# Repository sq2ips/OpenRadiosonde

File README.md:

# OpenRadiosonde

This project has a goal of making a open source amateur radiosonde project for high altitude balloon flights with telemetry and images downlink.

# Main features:
  - Dual band 100mW transmitter 2m and 70cm
  - Horus Binary V3 4FSK and AFSK APRS telemetry encoder
  - SSTV encoder
  - camera and other sensors connector
  - Battery voltage ADC
  - GPS positioning

# Hardware
  - STM32L476RGT6 MCU
  - SI4468-A2A-IMR Radio transmitter
  - 30MHz TCXO
  - u-blox GPS???
  - camera?
  - PSU?

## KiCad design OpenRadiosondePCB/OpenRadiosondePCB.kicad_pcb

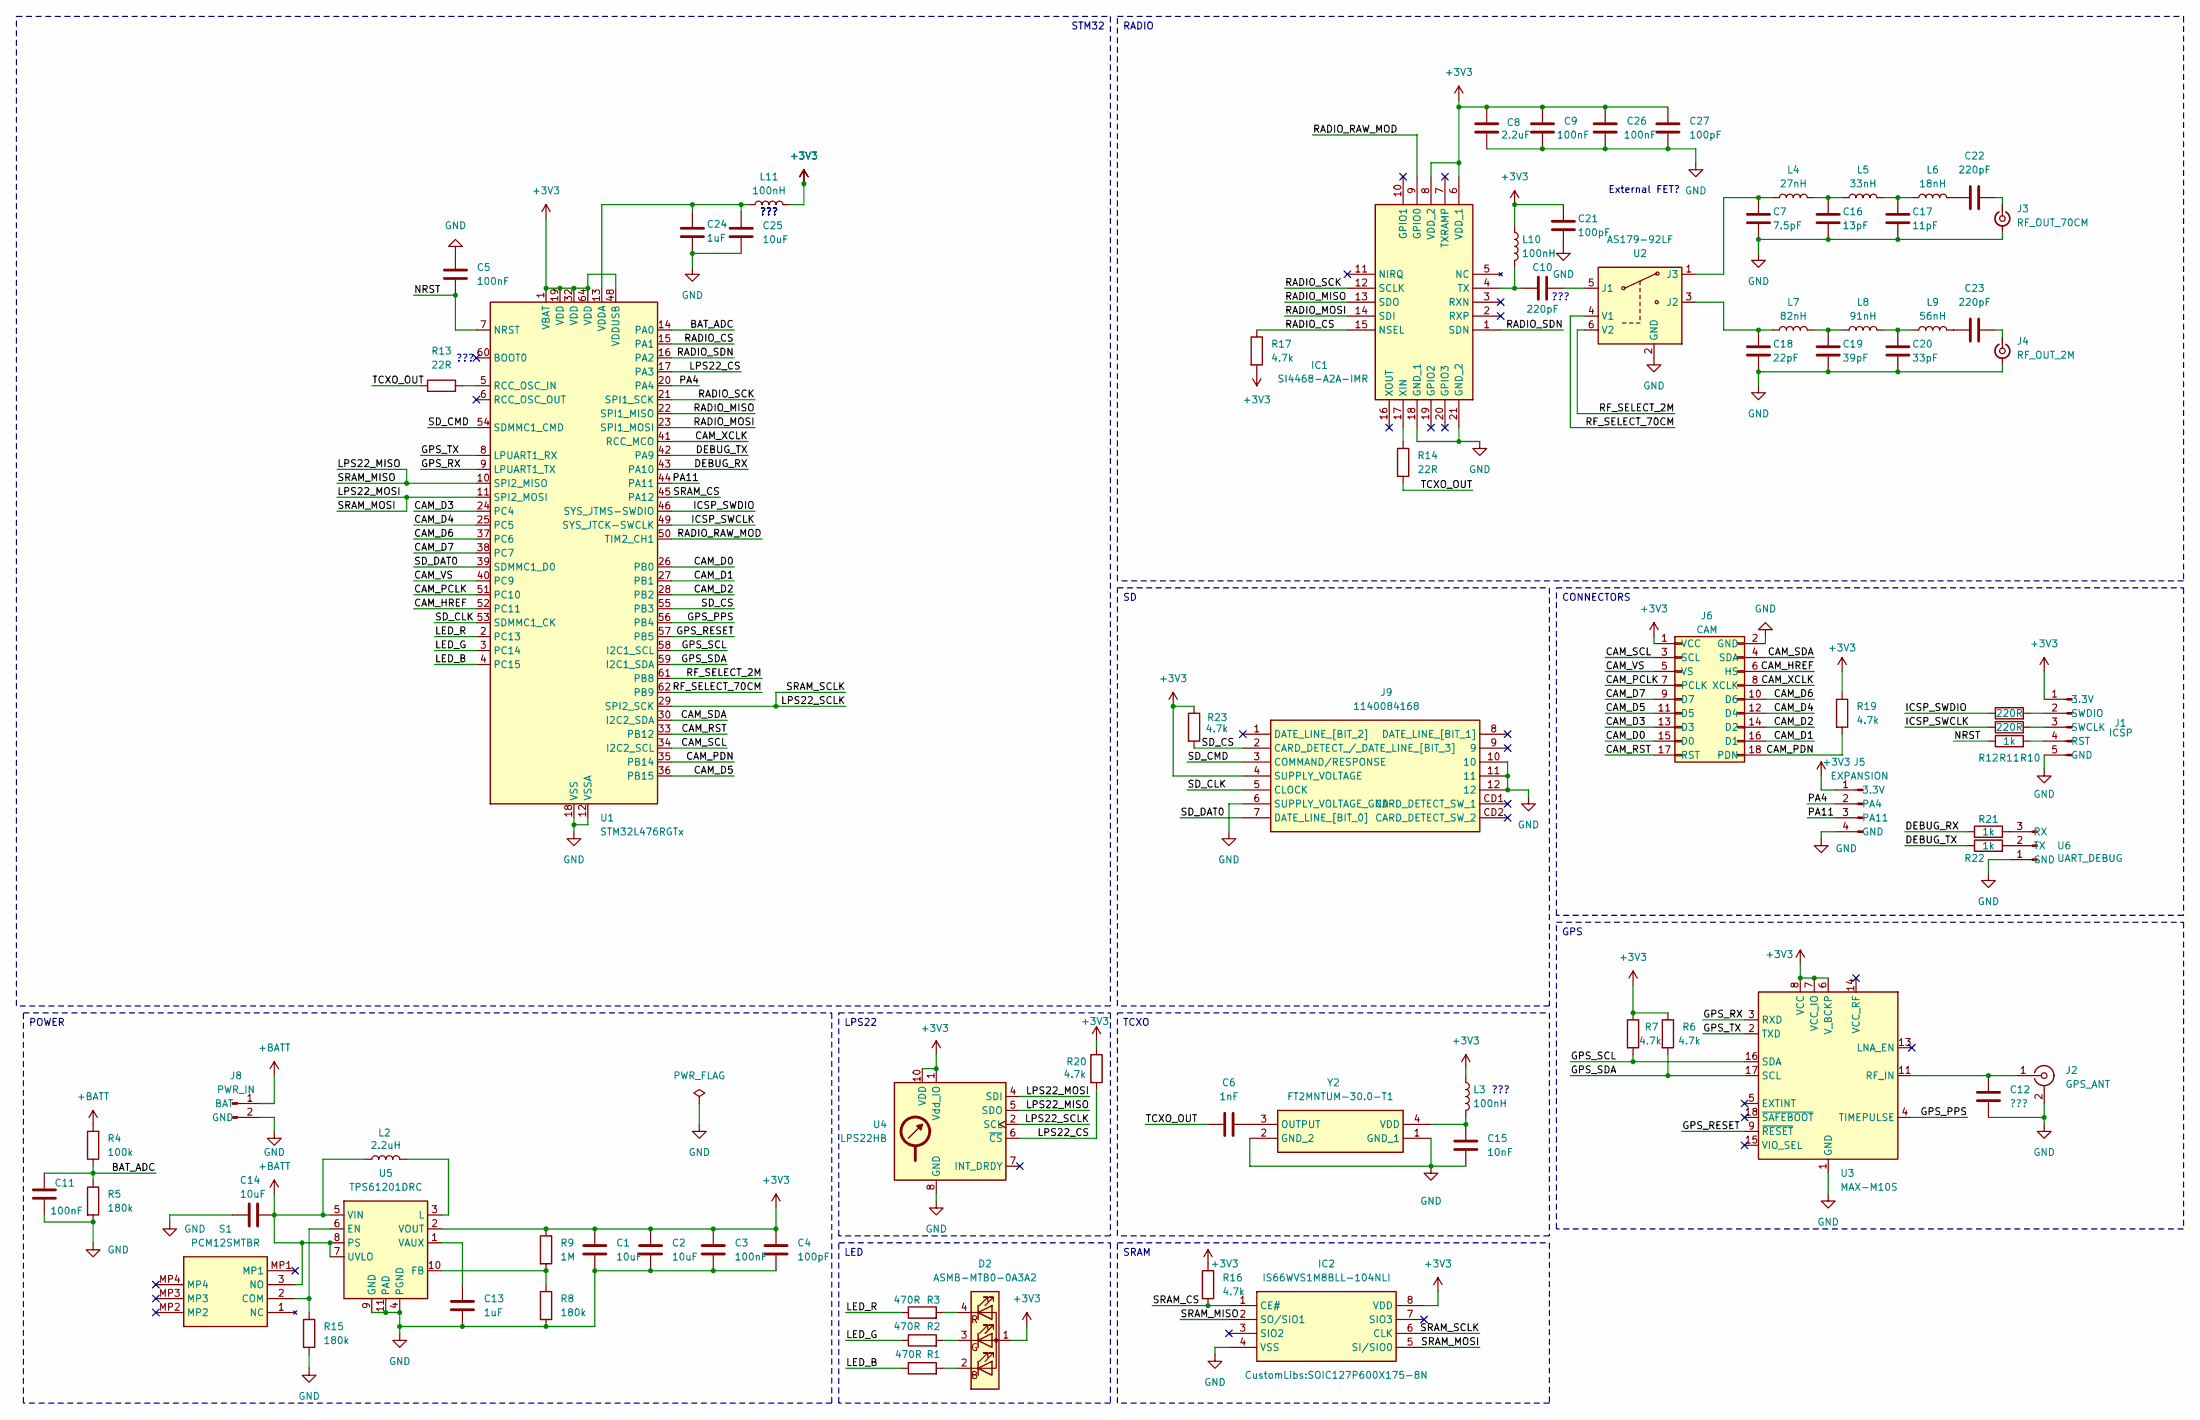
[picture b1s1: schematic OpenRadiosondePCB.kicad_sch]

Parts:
C1, C2, C14, C25: 10uF; C_0603_1608Metric
C3, C5, C9, C11, C26: 100nF; C_0603_1608Metric
C4, C21, C27: 100pF; C_0603_1608Metric
C6: 1nF; C_0603_1608Metric
C7: 7.5pF; C_0603_1608Metric
C8: 2.2uF; C_0603_1608Metric
C10, C22, C23: 220pF; C_0603_1608Metric
C12: ???; C_0603_1608Metric
C13, C24: 1uF; C_0603_1608Metric
C15: 10nF; C_0603_1608Metric
C16: 13pF; C_0603_1608Metric
C17: 11pF; C_0603_1608Metric
C18: 22pF; C_0603_1608Metric
C19: 39pF; C_0603_1608Metric
C20: 33pF; C_0603_1608Metric
D2: ASMB-MTB0-0A3A2; LED_Avago_PLCC4_3.2x2.8mm_CW
IC1: SI4468-A2A-IMR; QFN50P400X400X90-21N; Mouser Part Number 634-SI4468-A2A-IMR
IC2: IS66WVS1M8BLL-104NLI; SOIC127P600X175-8N; Mouser Part Number 870-ISS1M8BLL-104NLI
J1: ICSP; PinHeader_1x05_P2.54mm_Vertical
J2: GPS_ANT; U.FL_Hirose_U.FL-R-SMT-1_Vertical
J3: RF_OUT_70CM; SMA_Molex_73251-1153_EdgeMount_Horizontal
J4: RF_OUT_2M; SMA_Molex_73251-1153_EdgeMount_Horizontal
J5: EXPANSION; PinHeader_1x04_P2.54mm_Vertical
J6: CAM; PinHeader_2x09_P2.54mm_Vertical
J8: PWR_IN; PinHeader_1x02_P2.54mm_Vertical
J9: 1140084168; Mouser Part Number 523-114-00841-68
L2: 2.2uH; LPS3015
L3, L10, L11: 100nH; L_0603_1608Metric
L4: 27nH; L_0603_1608Metric
L5: 33nH; L_0603_1608Metric
L6: 18nH; L_0603_1608Metric
L7: 82nH; L_0603_1608Metric
L8: 91nH; L_0603_1608Metric
L9: 56nH; L_0603_1608Metric
R1, R2, R3: 470R; R_0603_1608Metric
R4: 100k; R_0603_1608Metric
R5, R8, R15: 180k; R_0603_1608Metric
R6, R7, R16, R17, R19, R20, R23: 4.7k; R_0603_1608Metric
R9: 1M; R_0603_1608Metric
R10, R21, R22: 1k; R_0603_1608Metric
R11, R12: 220R; R_0603_1608Metric
R13, R14: 22R; R_0603_1608Metric
S1: PCM12SMTBR; Mouser Part Number 611-PCM12SMTBR
U1: STM32L476RGTx; LQFP-64_10x10mm_P0.5mm
U2: AS179-92LF; SOT-363_SC-70-6
U3: MAX-M10S; ublox_MAX
U4: LPS22HB; ST_HLGA-10_2x2mm_P0.5mm_LayoutBorder3x2y
U5: TPS61201DRC; Texas_S-PVSON-N10_ThermalVias
U6: UART_DEBUG; PinHeader_1x03_P2.54mm_Vertical
Y2: FT2MNTUM-30.0-T1; FT2MNTUM300T1; Mouser Part Number 815-FT2MNTUM-30.0-T1

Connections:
+3V3: C1.1, C2.1, C3.1, C4.1, C8.1, C9.1, C21.1, C26.1, C27.1, D2.1 (A), IC1.6 (VDD_1), IC1.8 (VDD_2), IC2.8 (VDD), J1.1 (3.3V), J5.1 (3.3V), J6.1 (VCC), J9.4 (SUPPLY_VOLTAGE), L3.1, L10.1, L11.2, R6.1, R7.1, R9.1, R16.1, R17.2, R19.1, R20.1, R23.1, U1.1 (VBAT), U1.19 (VDD), U1.32 (VDD), U1.48 (VDDUSB), U1.64 (VDD), U3.6 (V_BCKP), U3.7 (VCC_IO), U3.8 (VCC), U4.1 (Vdd_IO), U4.10 (VDD), U5.2 (VOUT)
+BATT: C14.1, J8.1 (BAT), L2.1, R4.2, S1.3 (NO), U5.5 (VIN), U5.7 (UVLO), U5.8 (PS)
/BAT_ADC: C11.1, R4.1, R5.1, U1.14 (PA0)
/CAM_D0: J6.15 (D0), U1.26 (PB0)
/CAM_D1: J6.16 (D1), U1.27 (PB1)
/CAM_D2: J6.14 (D2), U1.28 (PB2)
/CAM_D3: J6.13 (D3), U1.24 (PC4)
/CAM_D4: J6.12 (D4), U1.25 (PC5)
/CAM_D5: J6.11 (D5), U1.36 (PB15)
/CAM_D6: J6.10 (D6), U1.37 (PC6)
/CAM_D7: J6.9 (D7), U1.38 (PC7)
/CAM_HREF: J6.6 (HS), U1.52 (PC11)
/CAM_PCLK: J6.7 (PCLK), U1.51 (PC10)
/CAM_PDN: J6.18 (PDN), R19.2, U1.35 (PB14)
/CAM_RST: J6.17 (RST), U1.33 (PB12)
/CAM_SCL: J6.3 (SCL), U1.34 (I2C2_SCL)
/CAM_SDA: J6.4 (SDA), U1.30 (I2C2_SDA)
/CAM_VS: J6.5 (VS), U1.40 (PC9)
/CAM_XCLK: J6.8 (XCLK), U1.41 (RCC_MCO)
/DEBUG_RX: R21.1, U1.43 (PA10)
/DEBUG_TX: R22.1, U1.42 (PA9)
/GPS_PPS: U1.56 (PB4), U3.4 (TIMEPULSE)
/GPS_RESET: U1.57 (PB5), U3.9 (~RESET)
/GPS_RX: U1.9 (LPUART1_TX), U3.3 (RXD)
/GPS_SCL: R7.2, U1.58 (I2C1_SCL), U3.16 (SDA)
/GPS_SDA: R6.2, U1.59 (I2C1_SDA), U3.17 (SCL)
/GPS_TX: U1.8 (LPUART1_RX), U3.2 (TXD)
/ICSP_SWCLK: R11.1, U1.49 (SYS_JTCK-SWCLK)
/ICSP_SWDIO: R12.1, U1.46 (SYS_JTMS-SWDIO)
/LED_B: R1.1, U1.4 (PC15)
/LED_G: R2.1, U1.3 (PC14)
/LED_R: R3.1, U1.2 (PC13)
/LPS22_CS: R20.2, U1.17 (PA3), U4.6 (~CS)
/LPS22_MISO: IC2.2 (SO/SIO1), U1.10 (SPI2_MISO), U4.5 (SDO)
/LPS22_MOSI: IC2.5 (SI/SIO0), U1.11 (SPI2_MOSI), U4.4 (SDI)
/LPS22_SCLK: IC2.6 (CLK), U1.29 (SPI2_SCK), U4.2 (SCL)
/NRST: C5.2, R10.1, U1.7 (NRST)
/PA4: J5.2 (PA4), U1.20 (PA4)
/PA11: J5.3 (PA11), U1.44 (PA11)
/RADIO_CS: IC1.15 (NSEL), R17.1, U1.15 (PA1)
/RADIO_MISO: IC1.13 (SDO), U1.22 (SPI1_MISO)
/RADIO_MOSI: IC1.14 (SDI), U1.23 (SPI1_MOSI)
/RADIO_RAW_MOD: IC1.9 (GPIO0), U1.50 (TIM2_CH1)
/RADIO_SCK: IC1.12 (SCLK), U1.21 (SPI1_SCK)
/RADIO_SDN: IC1.1 (SDN), U1.16 (PA2)
/RF_SELECT_2M: U1.61 (PB8), U2.6 (V2)
/RF_SELECT_70CM: U1.62 (PB9), U2.4 (V1)
/SD_CLK: J9.5 (CLOCK), U1.53 (SDMMC1_CK)
/SD_CMD: J9.3 (COMMAND/RESPONSE), U1.54 (SDMMC1_CMD)
/SD_CS: J9.2 (CARD_DETECT_/_DATE_LINE_[BIT_3]), R23.2, U1.55 (PB3)
/SD_DAT0: J9.7 (DATE_LINE_[BIT_0]), U1.39 (SDMMC1_D0)
/SRAM_CS: IC2.1 (CE#), R16.2, U1.45 (PA12)
/TCXO_OUT: C6.2, R13.1, R14.2
GND: C1.2, C2.2, C3.2, C4.2, C5.1, C7.2, C8.2, C9.2, C11.2, C12.2, C13.1, C14.2, C15.2, C16.2, C17.2, C18.2, C19.2, C20.2, C21.2, C24.2, C25.2, C26.2, C27.2, IC1.18 (GND_1), IC1.21 (GND_2), IC2.4 (VSS), J1.5 (GND), J2.2 (Ext), J3.2 (Ext), J4.2 (Ext), J5.4 (GND), J6.2 (GND), J8.2 (GND), J9.6 (SUPPLY_VOLTAGE_GND), J9.10, J9.11, J9.12, R5.2, R8.2, R15.2, U1.12 (VSSA), U1.18 (VSS), U1.31 (VSS), U1.47 (VSS), U1.63 (VSS), U2.2 (GND), U3.1 (GND), U3.10 (GND), U3.12 (GND), U4.3 (GND), U4.8 (GND), U4.9 (GND), U5.4 (PGND), U5.9 (GND), U5.11 (PAD), U6.1 (GND), Y2.1 (GND_1), Y2.2 (GND_2)
unnamed: C16.1, L4.2, L5.1
unnamed: C17.1, L5.2, L6.1
unnamed: C19.1, L7.2, L8.1
unnamed: C20.1, L8.2, L9.1
unnamed: C22.1, L6.2
unnamed: C23.1, L9.2
unnamed: D2.2 (BK), R1.2
unnamed: D2.3 (GK), R2.2
unnamed: D2.4 (RK), R3.2
unnamed: C10.1, IC1.4 (TX), L10.2
unnamed: IC1.17 (XIN), R14.1
unnamed: J1.4 (RST), R10.2
unnamed: J1.3 (SWCLK), R11.2
unnamed: J1.2 (SWDIO), R12.2
unnamed: C12.1, J2.1 (In), U3.11 (RF_IN)
unnamed: C22.2, J3.1 (In)
unnamed: C23.2, J4.1 (In)
unnamed: R15.1, S1.2 (COM), U5.6 (EN)
unnamed: R13.2, U1.5 (RCC_OSC_IN)
unnamed: C24.1, C25.1, L11.1, U1.13 (VDDA)
unnamed: C10.2, U2.5 (J1)
unnamed: C18.1, L7.1, U2.3 (J2)
unnamed: C7.1, L4.1, U2.1 (J3)
unnamed: R8.1, R9.2, U5.10 (FB)
unnamed: L2.2, U5.3 (L)
unnamed: C13.2, U5.1 (VAUX)
unnamed: R21.2, U6.3 (RX)
unnamed: R22.2, U6.2 (TX)
unnamed: C6.1, Y2.3 (OUTPUT)
unnamed: C15.1, L3.2, Y2.4 (VDD)

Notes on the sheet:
???
???
External FET?
TCXO
POWER
SRAM
STM32
LED
CONNECTORS
LPS22
GPS
RADIO

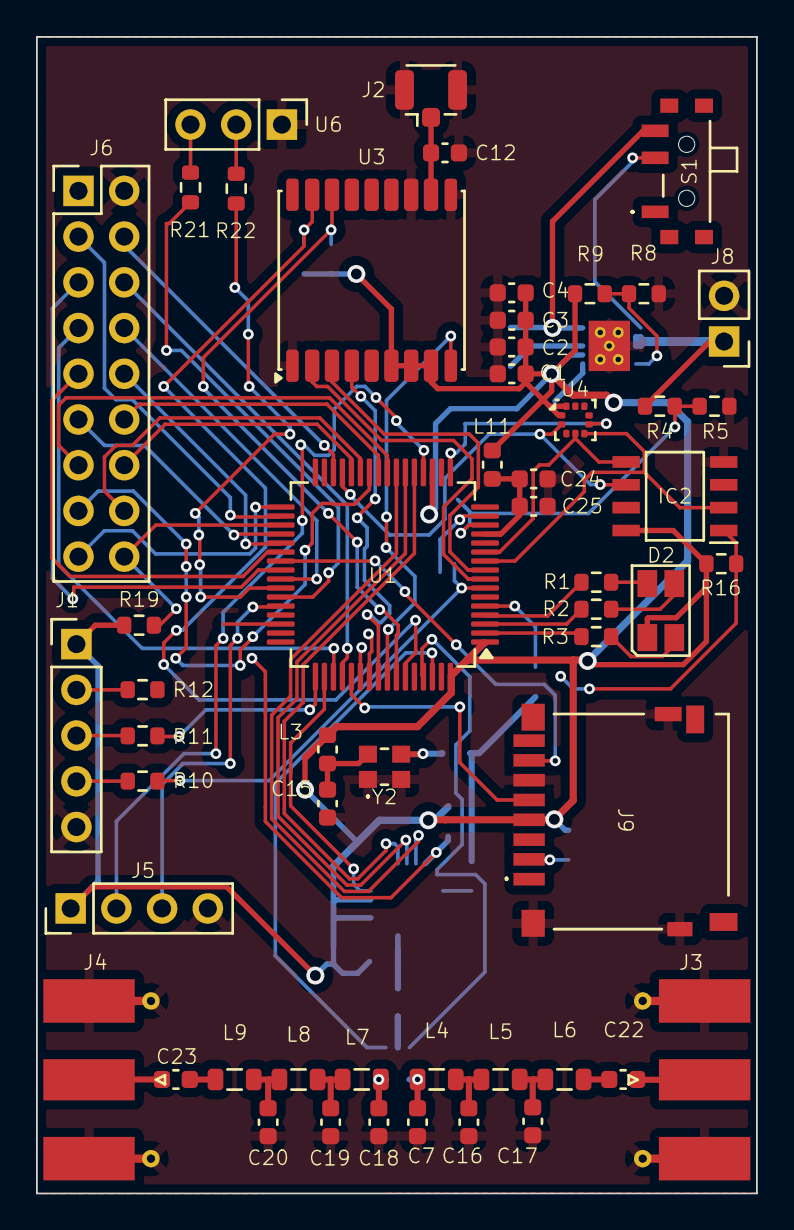
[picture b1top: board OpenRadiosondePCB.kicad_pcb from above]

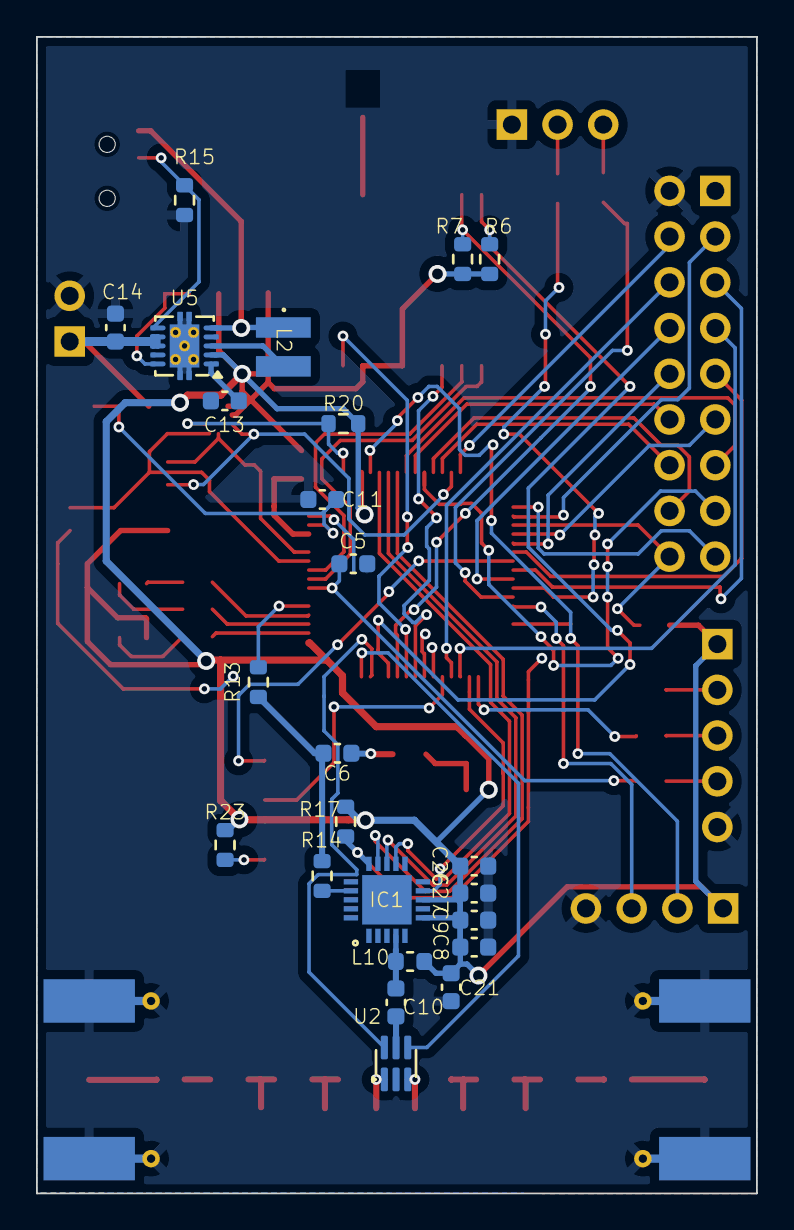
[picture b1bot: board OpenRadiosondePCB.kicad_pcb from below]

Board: 2 copper layers, 40.0 x 64.2 mm, 78 parts (24 on the bottom side), 84 nets.

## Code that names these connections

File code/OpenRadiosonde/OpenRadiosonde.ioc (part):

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Mcu.Name=STM32L476R(C-E-G)Tx
Mcu.Package=LQFP64
Mcu.UserName=STM32L476RGTx
PA0.GPIOParameters=GPIO_Label
PA0.GPIO_Label=BAT_ADC
PA0.Signal=ADCx_IN5
PA1.GPIOParameters=GPIO_Label
PA1.GPIO_Label=RADIO_CS
PA1.Signal=GPIO_Output
PA10.Mode=Asynchronous
PA10.Signal=USART1_RX
PA13\ (JTMS-SWDIO).Mode=Serial_Wire
PA13\ (JTMS-SWDIO).Signal=SYS_JTMS-SWDIO
PA14\ (JTCK-SWCLK).Mode=Serial_Wire
PA14\ (JTCK-SWCLK).Signal=SYS_JTCK-SWCLK
PA15\ (JTDI).GPIOParameters=GPIO_Label
PA15\ (JTDI).GPIO_Label=RADIO_RAW_MOD
PA15\ (JTDI).Signal=S_TIM2_CH1
PA2.GPIOParameters=GPIO_Label
PA2.GPIO_Label=RADIO_SDN
PA2.Signal=GPIO_Output
PA3.GPIOParameters=GPIO_Label
PA3.GPIO_Label=LPS22_CS
PA3.Signal=GPIO_Output
PA5.GPIOParameters=GPIO_Label
PA5.GPIO_Label=RADIO_SCK
PA5.Mode=Full_Duplex_Master
PA5.Signal=SPI1_SCK
PA6.GPIOParameters=GPIO_Label
PA6.GPIO_Label=RADIO_MISO
PA6.Mode=Full_Duplex_Master
PA6.Signal=SPI1_MISO
PA7.GPIOParameters=GPIO_Label
PA7.GPIO_Label=RADIO_MOSI
PA7.Mode=Full_Duplex_Master
PA7.Signal=SPI1_MOSI
PA8.GPIOParameters=GPIO_Label
PA8.GPIO_Label=CAM_XCLK
PA8.Mode=Clock-out
PA8.Signal=RCC_MCO
PA9.Mode=Asynchronous
PA9.Signal=USART1_TX
PB0.GPIOParameters=GPIO_Label
PB0.GPIO_Label=CAM_D0
PB0.Signal=GPIO_Input
PB1.GPIOParameters=GPIO_Label
PB1.GPIO_Label=CAM_D1
PB1.Signal=GPIO_Input
PB10.GPIOParameters=GPIO_Label
PB10.GPIO_Label=LPS22_SCK
PB10.Mode=Full_Duplex_Master
PB10.Signal=SPI2_SCK
PB11.GPIOParameters=GPIO_Label
PB11.GPIO_Label=CAM_SDA
PB11.Mode=I2C
PB11.Signal=I2C2_SDA
PB12.GPIOParameters=GPIO_Label
PB12.GPIO_Label=CAM_RST
PB12.Signal=GPIO_Output
PB13.GPIOParameters=GPIO_Label
PB13.GPIO_Label=CAM_SCL
PB13.Mode=I2C
PB13.Signal=I2C2_SCL
PB14.GPIOParameters=GPIO_Label
PB14.GPIO_Label=CAM_PDN
PB14.Signal=GPIO_Output
PB15.GPIOParameters=GPIO_Label
PB15.GPIO_Label=CAM_D5
PB15.Signal=GPIO_Input
PB2.GPIOParameters=GPIO_Label
PB2.GPIO_Label=CAM_D2
PB2.Signal=GPIO_Input
PB3\ (JTDO-TRACESWO).GPIOParameters=GPIO_Label
PB3\ (JTDO-TRACESWO).GPIO_Label=SD_CS
PB3\ (JTDO-TRACESWO).Signal=GPIO_Output
PB4\ (NJTRST).GPIOParameters=GPIO_Label
PB4\ (NJTRST).GPIO_Label=GPS_PPS
PB4\ (NJTRST).Signal=GPXTI4
PB5.GPIOParameters=GPIO_Label
PB5.GPIO_Label=GPS_RESET
PB5.Signal=GPIO_Output
PB6.Mode=I2C
PB6.Signal=I2C1_SCL
PB7.Mode=I2C
PB7.Signal=I2C1_SDA
PB8.GPIOParameters=GPIO_Label
PB8.GPIO_Label=RADIO_SELECT_2M
PB8.Signal=GPIO_Output
PB9.GPIOParameters=GPIO_Label
PB9.GPIO_Label=RADIO_SELECT_70CM
PB9.Signal=GPIO_Output
PC0.GPIOParameters=GPIO_Label
PC0.GPIO_Label=GPS_MRX
PC0.Mode=Asynchronous
PC0.Signal=LPUART1_RX
PC1.GPIOParameters=GPIO_Label
PC1.GPIO_Label=GPS_MTX
PC1.Mode=Asynchronous
PC1.Signal=LPUART1_TX
PC10.GPIOParameters=GPIO_Label
PC10.GPIO_Label=CAM_HREF
PC10.Signal=GPIO_Output
PC11.GPIOParameters=GPIO_Label
PC11.GPIO_Label=CAM_PCLK
PC11.Signal=GPIO_Input
PC12.Mode=SD_1_bit
PC12.Signal=SDMMC1_CK
PC13.GPIOParameters=GPIO_Label
PC13.GPIO_Label=LED_R
PC13.Signal=GPIO_Output
PC14-OSC32_IN\ (PC14).GPIOParameters=GPIO_Label
PC14-OSC32_IN\ (PC14).GPIO_Label=LED_G
PC14-OSC32_IN\ (PC14).Signal=GPIO_Output
PC15-OSC32_OUT\ (PC15).GPIOParameters=GPIO_Label
PC15-OSC32_OUT\ (PC15).GPIO_Label=LED_B
PC15-OSC32_OUT\ (PC15).Signal=GPIO_Output
PC2.GPIOParameters=GPIO_Label
PC2.GPIO_Label=LPS22_MISO
PC2.Mode=Full_Duplex_Master
PC2.Signal=SPI2_MISO
PC3.GPIOParameters=GPIO_Label
PC3.GPIO_Label=LPS22_MOSI
PC3.Mode=Full_Duplex_Master
PC3.Signal=SPI2_MOSI
PC4.GPIOParameters=GPIO_Label
PC4.GPIO_Label=CAM_D3
PC4.Signal=GPIO_Input
PC5.GPIOParameters=GPIO_Label
PC5.GPIO_Label=CAM_D4
PC5.Signal=GPIO_Input
PC6.GPIOParameters=GPIO_Label
PC6.GPIO_Label=CAM_D6
PC6.Signal=GPIO_Input
PC7.GPIOParameters=GPIO_Label
PC7.GPIO_Label=CAM_D7
PC7.Signal=GPIO_Input
PC8.Mode=SD_1_bit
PC8.Signal=SDMMC1_D0
PC9.GPIOParameters=GPIO_Label
PC9.GPIO_Label=CAM_VSYNC
PC9.Signal=GPIO_Input
PD2.Mode=SD_1_bit
PD2.Signal=SDMMC1_CMD
PH0-OSC_IN\ (PH0).Mode=HSE-External-Oscillator
PH0-OSC_IN\ (PH0).Signal=RCC_OSC_IN
PH1-OSC_OUT\ (PH1).Mode=HSE-External-Oscillator
PH1-OSC_OUT\ (PH1).Signal=RCC_OSC_OUT
RCC.HSE_VALUE=30000000
RCC.SYSCLKFreq_VALUE=60000000
RCC.SYSCLKSource=RCC_SYSCLKSOURCE_PLLCLK
board=custom

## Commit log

2026-02-19 Added kicad project
2026-02-19 Readme info
2026-02-19 First components and custom footprints
2026-02-19 Update gitignore
2026-02-19 Schematics inital work
2026-02-20 Further PCB design and added CubeMX project
2026-02-20 Further PCB work
2026-02-21 More PCB work
2026-02-21 Added cammera, SRAM, LPS22 and more, changed MX project, more pin considerations, some schematics cleanup.
2026-02-23 Finalizing schematic, some more pin changes
2026-03-02 Working on PCB design
2026-03-02 Rounting (almost) all traces again.
